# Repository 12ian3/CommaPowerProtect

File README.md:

# Comma Power Protect
The comma 2 draws 50mA even while powered off. This is just too much. The calcuation shows that this should last 30 days before fully discharging your car battery, but that's a 100% discharge. You still need some amount of charge in the battery to start your engine. For me, that was about 12 days.  
This project aims to improve upon the stock comma power by adding an adjustable voltage cutoff to the comma power. Thus, when you turn off your car*, the device will discharge your battery down to your set threshold, and then fully turn off**.  
  
Notes:  
\*On some vehicles, the relay harness always provides 12v I believe. On those vehicles, this would prove ineffective.  
\**Leakage current of around 10uA.

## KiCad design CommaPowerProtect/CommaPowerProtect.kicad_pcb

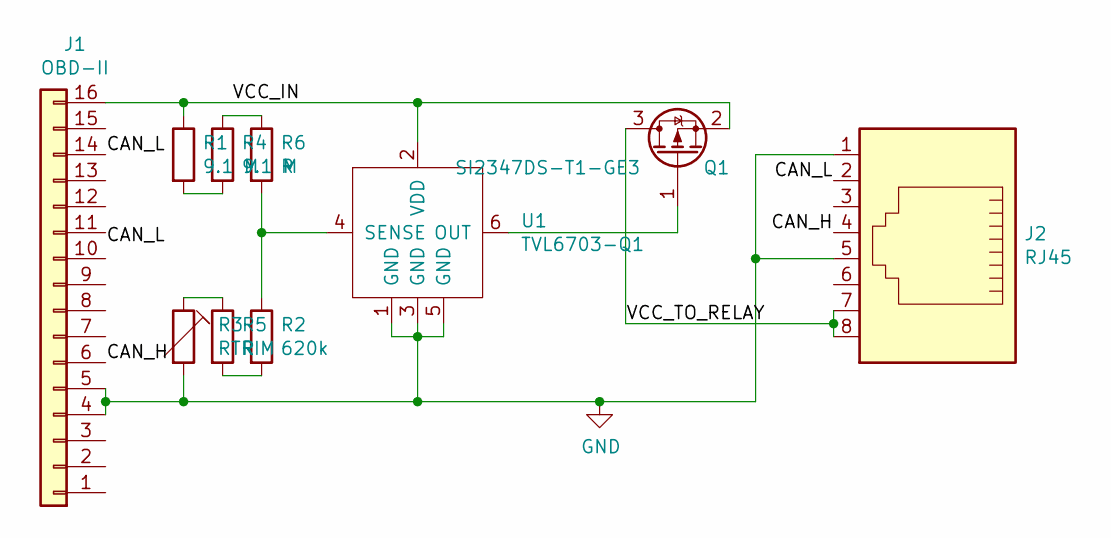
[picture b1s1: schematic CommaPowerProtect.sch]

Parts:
J1: OBD-II; OBDii
J2: RJ45; 634008137521
Q1: SI2347DS-T1-GE3; SOT-23
R1, R4: 9.1 M; R_0603_1608Metric_Pad0.98x0.95mm_HandSolder
R2: 620k; R_0603_1608Metric_Pad0.98x0.95mm_HandSolder
R3: RTRIM; Potentiometer_Bourns_TC33X_Vertical
R5, R6: R; R_0603_1608Metric_Pad0.98x0.95mm_HandSolder
U1: TVL6703-Q1; WSON-6_1.5x1.5mm_P0.5mm

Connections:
/CAN_H: J1.6, J2.4
/CAN_L: J1.14, J2.2
/VCC_IN: J1.16, Q1.2 (S), R1.1, U1.2 (VDD)
/VCC_TO_RELAY: J2.7, J2.8, Q1.3 (D)
GND: J1.4, J1.5, J2.1, J2.5, R3.2, U1.1 (GND), U1.3 (GND), U1.5 (GND)
unnamed: Q1.1 (G), U1.6 (OUT)
unnamed: R1.2, R4.2
unnamed: R2.1, R6.2, U1.4 (SENSE)
unnamed: R2.2, R5.2
unnamed: R3.1, R5.1
unnamed: R4.1, R6.1

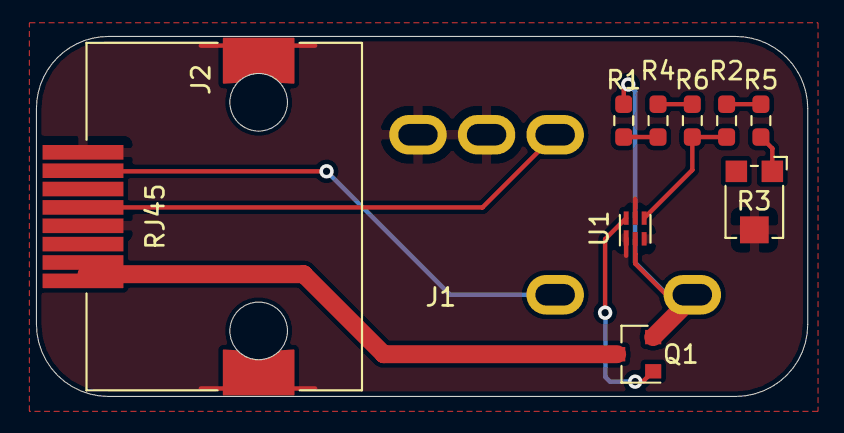
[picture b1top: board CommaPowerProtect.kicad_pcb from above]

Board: 2 copper layers, 42.9 x 20.0 mm, 10 parts (0 on the bottom side), 11 nets.

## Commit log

2022-01-27 File upload and repo init
2022-01-27 add readme
